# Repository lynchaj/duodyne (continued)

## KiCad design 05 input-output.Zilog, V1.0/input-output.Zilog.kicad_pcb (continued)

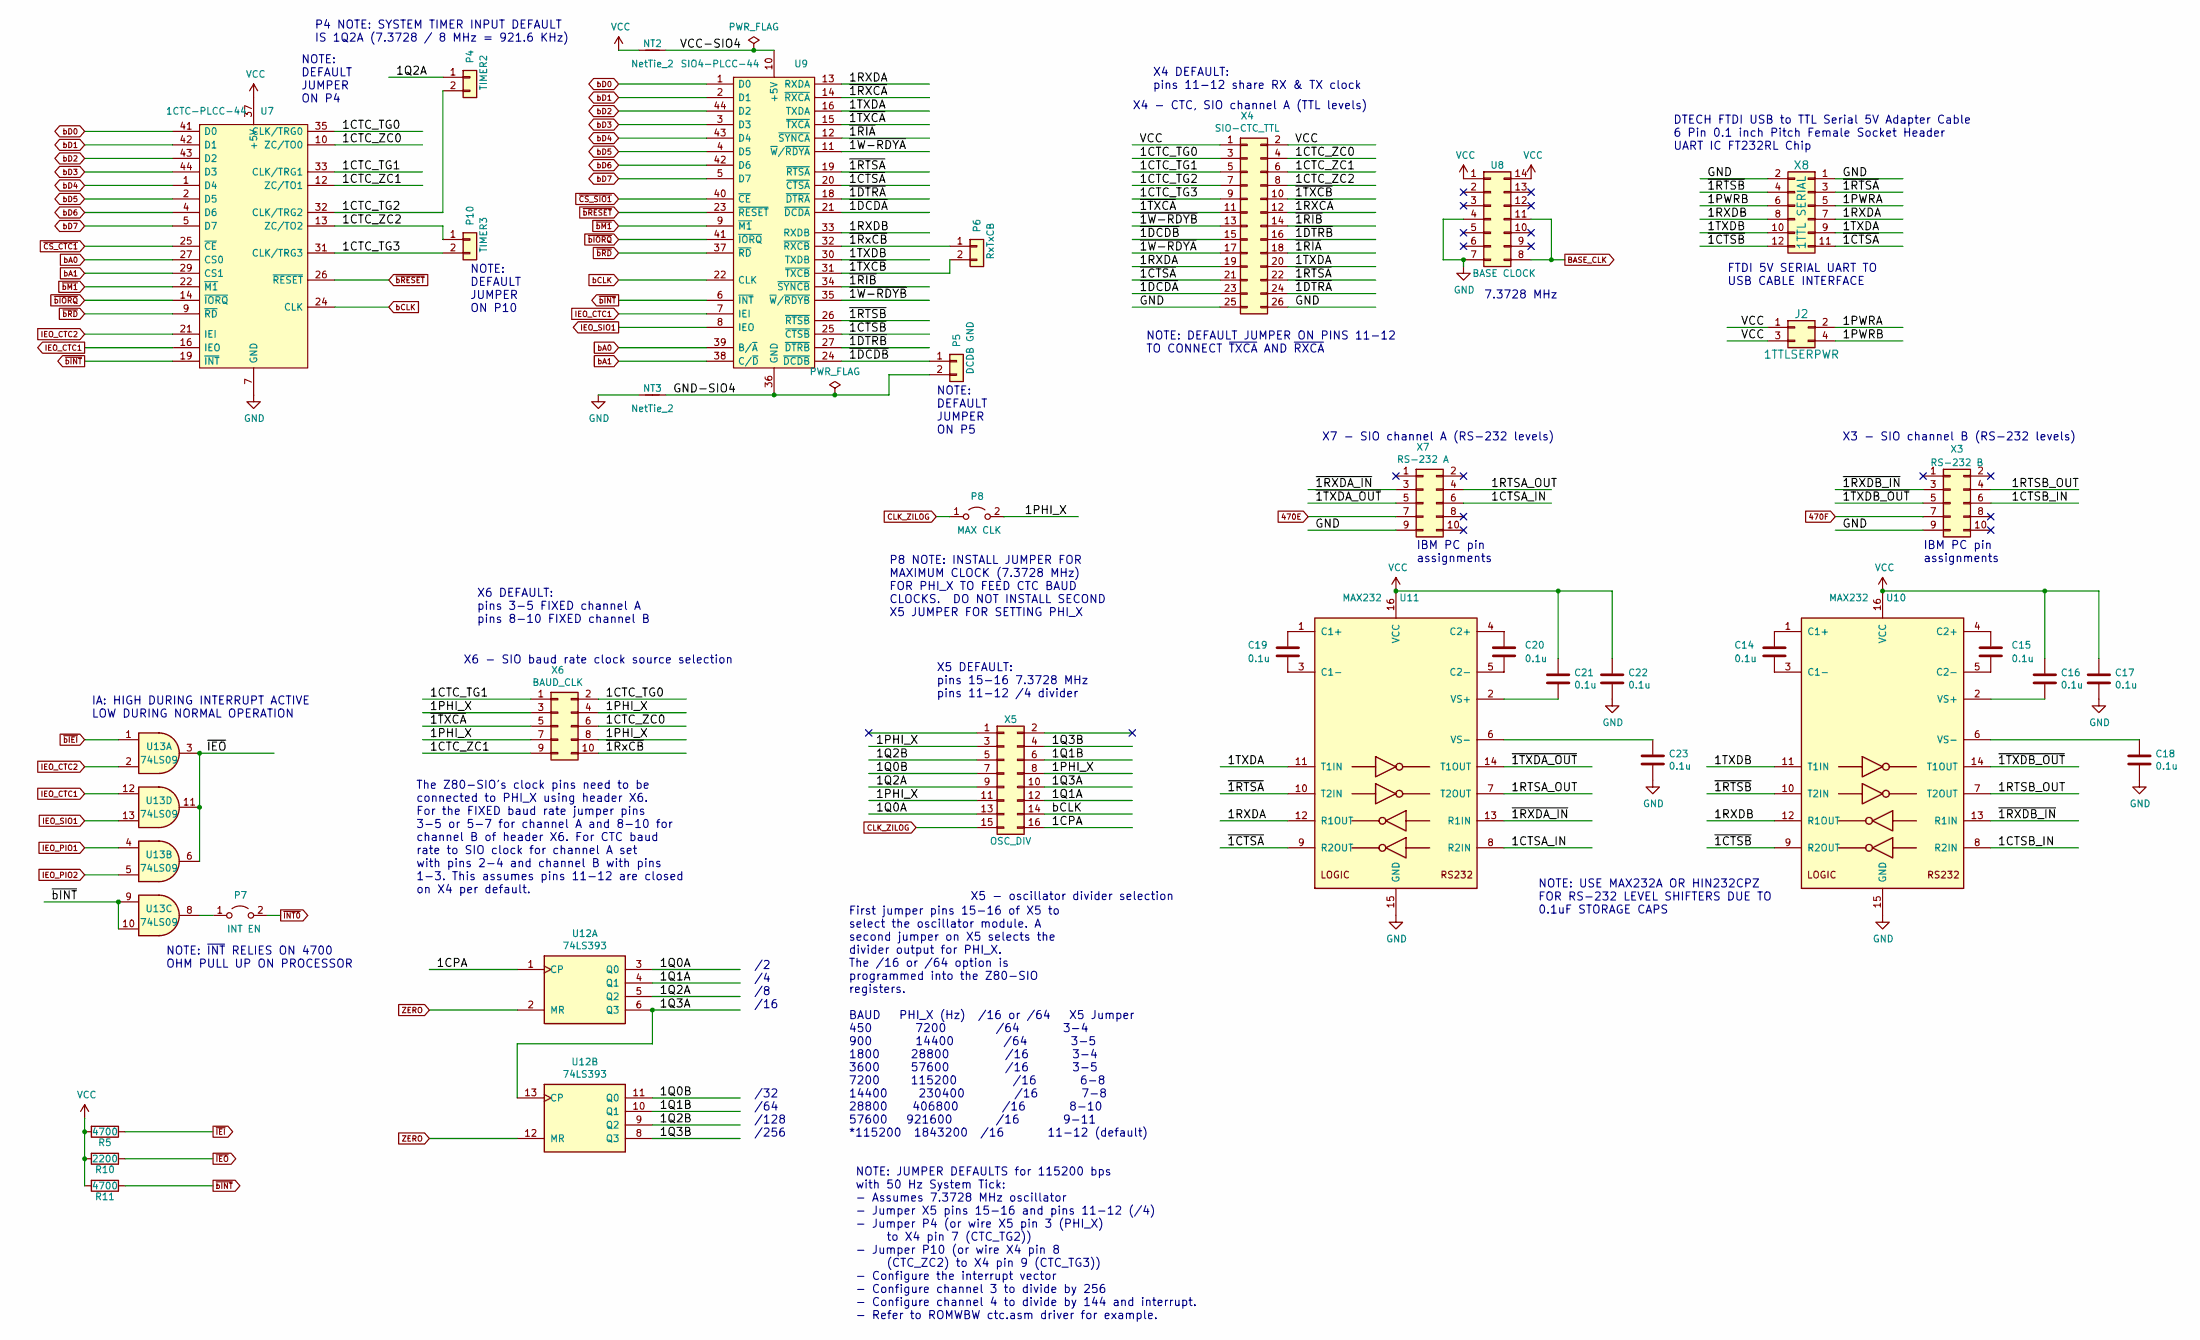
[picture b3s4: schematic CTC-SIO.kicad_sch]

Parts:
C14, C15, C16, C17, C18, C19, C20, C21, C22, C23: 0.1u; C_Disc_D5.0mm_W2.5mm_P5.00mm
J2: 1TTLSERPWR; PinHeader_2x02_P2.54mm_Vertical
NT2, NT3: NetTie_2; NetTie-2_THT_Pad0.3mm
P4: TIMER2; PinHeader_1x02_P2.54mm_Vertical
P5: DCDB GND; PinHeader_1x02_P2.54mm_Vertical
P6: RxTxCB; PinHeader_1x02_P2.54mm_Vertical
P7: INT EN; PinHeader_1x02_P2.54mm_Vertical
P8: MAX CLK; PinHeader_1x02_P2.54mm_Vertical
P10: TIMER3; PinHeader_1x02_P2.54mm_Vertical
R5, R11: 4700; R_Axial_DIN0207_L6.3mm_D2.5mm_P7.62mm_Horizontal
R10: 2200; R_Axial_DIN0207_L6.3mm_D2.5mm_P7.62mm_Horizontal
U7: 1CTC-PLCC-44; PLCC-44_THT-Socket; Manufacturer_Part_Number Z84C3010PEG; Mouser Part Number 692-Z84C3010PEG
U8: BASE CLOCK; DIP-14_W7.62mm
U9: SIO4-PLCC-44; PLCC-44_THT-Socket; Manufacturer_Part_Number Z84C4206PEG; Mouser Part Number 692-Z84C4206PEG
U10, U11: MAX232; DIP-16_W7.62mm
U12: 74LS393; DIP-14_W7.62mm
U13: 74LS09; DIP-14_W7.62mm
X3: RS-232 B; IDC-Header_2x05_P2.54mm_Horizontal
X4: SIO-CTC_TTL; PinHeader_2x13_P2.54mm_Vertical
X5: OSC_DIV; PinHeader_2x08_P2.54mm_Vertical
X6: BAUD_CLK; PinHeader_2x05_P2.54mm_Vertical
X7: RS-232 A; IDC-Header_2x05_P2.54mm_Horizontal
X8: 1TTL SERIAL; IDC-Header_2x06_P2.54mm_Horizontal

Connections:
470E: X7.7; also elsewhere on the board
470F: X3.7; also elsewhere on the board
/CTC-SIO/1CPA: U12.1 (CP), X5.16
/CTC-SIO/1CTC_TG0: U7.35 (CLK/TRG0), X4.3, X6.2
/CTC-SIO/1CTC_TG1: U7.33 (CLK/TRG1), X4.5, X6.1
/CTC-SIO/1CTC_TG2: P4.2, U7.32 (CLK/TRG2), X4.7
/CTC-SIO/1CTC_TG3: P10.2, U7.31 (CLK/TRG3), X4.9
/CTC-SIO/1CTC_ZC0: U7.10 (ZC/TO0), X4.4, X6.6
/CTC-SIO/1CTC_ZC1: U7.12 (ZC/TO1), X4.6, X6.9
/CTC-SIO/1CTC_ZC2: P10.1, U7.13 (ZC/TO2), X4.8
/CTC-SIO/1CTSA_IN: U11.8 (R2IN), X7.6
/CTC-SIO/1CTSB_IN: U10.8 (R2IN), X3.6
/CTC-SIO/1PHI_X: P8.2 (B), X5.3, X5.8, X5.11, X6.3, X6.4, X6.7, X6.8
/CTC-SIO/1PWRA: J2.2, X8.5
/CTC-SIO/1PWRB: J2.4, X8.6
/CTC-SIO/1Q0A: U12.3 (Q0), X5.13
/CTC-SIO/1Q0B: U12.11 (Q0), X5.7
/CTC-SIO/1Q1A: U12.4 (Q1), X5.12
/CTC-SIO/1Q1B: U12.10 (Q1), X5.6
/CTC-SIO/1Q2A: P4.1, U12.5 (Q2), X5.9
/CTC-SIO/1Q2B: U12.9 (Q2), X5.5
/CTC-SIO/1Q3A: U12.6 (Q3), U12.13 (CP), X5.10
/CTC-SIO/1Q3B: U12.8 (Q3), X5.4
/CTC-SIO/1RTSA_OUT: U11.7 (T2OUT), X7.4
/CTC-SIO/1RTSB_OUT: U10.7 (T2OUT), X3.4
/CTC-SIO/1RXDA: U9.13 (RXDA), U11.12 (R1OUT), X4.19, X8.7
/CTC-SIO/1RXDB: U9.33 (RXDB), U10.12 (R1OUT), X8.8
/CTC-SIO/1TXDA: U9.16 (TXDA), U11.11 (T1IN), X4.20, X8.9
/CTC-SIO/1TXDB: U9.30 (TXDB), U10.11 (T1IN), X8.10
/CTC-SIO/GND-SIO4: NT3.2, P5.2, U9.36 (GND)
/CTC-SIO/VCC-SIO4: NT2.2, U9.10 (+5V)
/CTC-SIO/~1CTSA: U9.20 (~CTSA), U11.9 (R2OUT), X4.21, X8.11
/CTC-SIO/~1CTSB: U9.25 (~CTSB), U10.9 (R2OUT), X8.12
/CTC-SIO/~1DCDA: U9.21 (~DCDA), X4.23
/CTC-SIO/~1DCDB: P5.1, U9.24 (~DCDB), X4.15
/CTC-SIO/~1DTRA: U9.18 (~DTRA), X4.24
/CTC-SIO/~1DTRB: U9.27 (~DTRB), X4.16
/CTC-SIO/~1RIA: U9.12 (~SYNCA), X4.18
/CTC-SIO/~1RIB: U9.34 (~SYNCB), X4.14
/CTC-SIO/~1RTSA: U9.19 (~RTSA), U11.10 (T2IN), X4.22, X8.3
/CTC-SIO/~1RTSB: U9.26 (~RTSB), U10.10 (T2IN), X8.4
/CTC-SIO/~1RXCA: U9.14 (~RXCA), X4.12
/CTC-SIO/~1RXDA_IN: U11.13 (R1IN), X7.3
/CTC-SIO/~1RXDB_IN: U10.13 (R1IN), X3.3
/CTC-SIO/~1RxCB: P6.1, U9.32 (~RXCB), X6.10
/CTC-SIO/~1TXCA: U9.15 (~TXCA), X4.11, X6.5
/CTC-SIO/~1TXCB: P6.2, U9.31 (~TXCB), X4.10
/CTC-SIO/~1TXDA_OUT: U11.14 (T1OUT), X7.5
/CTC-SIO/~1TXDB_OUT: U10.14 (T1OUT), X3.5
/CTC-SIO/~1W-RDYA: U9.11 (~W/~RDYA), X4.17
/CTC-SIO/~1W-RDYB: U9.35 (~W/~RDYB), X4.13
BASE_CLK: U8.8, U8.11; also elsewhere on the board
CLK_ZILOG: P8.1 (A), X5.15; also elsewhere on the board
GND: C17.2, C18.2, C22.2, C23.2, NT3.1, U7.7 (GND), U8.4, U8.7, U10.15 (GND), U11.15 (GND), X3.9, X4.25, X4.26, X7.9, X8.1, X8.2; also elsewhere on the board
IEO_CTC1: U7.16 (IEO), U9.7 (IEI), U13.12; also elsewhere on the board
IEO_CTC2: U7.21 (IEI), U13.2; also elsewhere on the board
IEO_PIO1: U13.4; also elsewhere on the board
IEO_PIO2: U13.5; also elsewhere on the board
IEO_SIO1: U9.8 (IEO), U13.13; also elsewhere on the board
unnamed: C14.1, U10.1 (C1+)
unnamed: C14.2, U10.3 (C1-)
unnamed: C15.1, U10.4 (C2+)
unnamed: C15.2, U10.5 (C2-)
unnamed: C16.2, U10.2 (VS+)
unnamed: C18.1, U10.6 (VS-)
unnamed: C19.1, U11.1 (C1+)
unnamed: C19.2, U11.3 (C1-)
unnamed: C20.1, U11.4 (C2+)
unnamed: C20.2, U11.5 (C2-)
unnamed: C21.2, U11.2 (VS+)
unnamed: C23.1, U11.6 (VS-)
unnamed: P7.1 (A), U13.8
VCC: C16.1, C17.1, C21.1, C22.1, J2.1, J2.3, NT2.1, R5.2, R10.2, R11.2, U7.37 (+5V), U8.1, U8.14, U10.16 (VCC), U11.16 (VCC), X4.1, X4.2; also elsewhere on the board
ZERO: U12.2 (MR), U12.12 (MR); also elsewhere on the board
bA0: U7.27 (CS0), U9.39 (B/~A); also elsewhere on the board
bA1: U7.29 (CS1), U9.38 (C/~D); also elsewhere on the board
bCLK: U7.24 (CLK), U9.22 (CLK), X5.14; also elsewhere on the board
bD0: U7.41 (D0), U9.1 (D0); also elsewhere on the board
bD1: U7.42 (D1), U9.2 (D1); also elsewhere on the board
bD2: U7.43 (D2), U9.44 (D2); also elsewhere on the board
bD3: U7.44 (D3), U9.3 (D3); also elsewhere on the board
bD4: U7.1 (D4), U9.43 (D4); also elsewhere on the board
bD5: U7.2 (D5), U9.4 (D5); also elsewhere on the board
bD6: U7.4 (D6), U9.42 (D6); also elsewhere on the board
bD7: U7.5 (D7), U9.5 (D7); also elsewhere on the board
~CS_CTC1: U7.25 (~CE); also elsewhere on the board
~CS_SIO1: U9.40 (~CE); also elsewhere on the board
~IEI: R5.1; also elsewhere on the board
~IEO: R10.1, U13.3, U13.6, U13.11; also elsewhere on the board
~INT0: P7.2 (B); also elsewhere on the board
~bIEI: U13.1; also elsewhere on the board
~bINT: R11.1, U7.19 (~INT), U9.6 (~INT), U13.9, U13.10; also elsewhere on the board
~bIORQ: U7.14 (~IORQ), U9.41 (~IORQ); also elsewhere on the board
~bM1: U7.22 (~M1), U9.9 (~M1); also elsewhere on the board
~bRD: U7.9 (~RD), U9.37 (~RD); also elsewhere on the board
~bRESET: U7.26 (~RESET), U9.23 (~RESET); also elsewhere on the board

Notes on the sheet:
NOTE: JUMPER DEFAULTS for 115200 bps with 50 Hz System Tick: - Assumes 7.3728 MHz oscillator - Jumper X5 pins 15-16 and pins 11-12 (/4) - Jumper P4 (or wire X5 pin 3 (PHI_X) to X4 pin 7 (CTC_TG2)) - Jumper P10 (or wire X4 pin 8 (CTC_ZC2) to X4 pin 9 (CTC_TG3)) - Configure the interrupt vector - Con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
X3 - SIO channel B (RS-232 levels)
The Z80-SIO's clock pins need to be connected to PHI_X using header X6. For the FIXED baud rate jumper pins 3-5 or 5-7 for channel A and 8-10 for channel B of header X6. For CTC baud rate to SIO clock for channel A set with pins 2-4 and channel B with pins 1-3. This assumes pins 11-12 are closed on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
X7 - SIO channel A (RS-232 levels)
DTECH FTDI USB to TTL Serial 5V Adapter Cable 6 Pin 0.1 inch Pitch Female Socket Header UART IC FT232RL Chip
NOTE: DEFAULT JUMPER ON P4
/32 /64 /128 /256
7.3728 MHz
NOTE: ~{INT} RELIES ON 4700 OHM PULL UP ON PROCESSOR
X5 - oscillator divider selection
FTDI 5V SERIAL UART TO USB CABLE INTERFACE
IBM PC pin assignments
P4 NOTE: SYSTEM TIMER INPUT DEFAULT IS 1Q2A (7.3728 / 8 MHz = 921.6 KHz)
IA: HIGH DURING INTERRUPT ACTIVE LOW DURING NORMAL OPERATION
NOTE: DEFAULT JUMPER ON P10
X5 DEFAULT: pins 15-16 7.3728 MHz pins 11-12 /4 divider
/2 /4 /8 /16
First jumper pins 15-16 of X5 to select the oscillator module. A second jumper on X5 selects the divider output for PHI_X. The /16 or /64 option is programmed into the Z80-SIO registers. BAUD PHI_X (Hz) /16 or /64 X5 Jumper 450 7200 /64 3-4 900 14400 /64 3-5 1800 28800 /16 3-4 3600 57600 /16 3-5 72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
NOTE: DEFAULT JUMPER ON PINS 11-12 TO CONNECT ~{TXCA} AND ~{RXCA}
X4 - CTC, SIO channel A (TTL levels)
NOTE: USE MAX232A OR HIN232CPZ FOR RS-232 LEVEL SHIFTERS DUE TO 0.1uF STORAGE CAPS
P8 NOTE: INSTALL JUMPER FOR MAXIMUM CLOCK (7.3728 MHz) FOR PHI_X TO FEED CTC BAUD CLOCKS. DO NOT INSTALL SECOND X5 JUMPER FOR SETTING PHI_X
X6 DEFAULT: pins 3-5 FIXED channel A pins 8-10 FIXED channel B
X6 - SIO baud rate clock source selection
X4 DEFAULT: pins 11-12 share RX & TX clock
NOTE: DEFAULT JUMPER ON P5

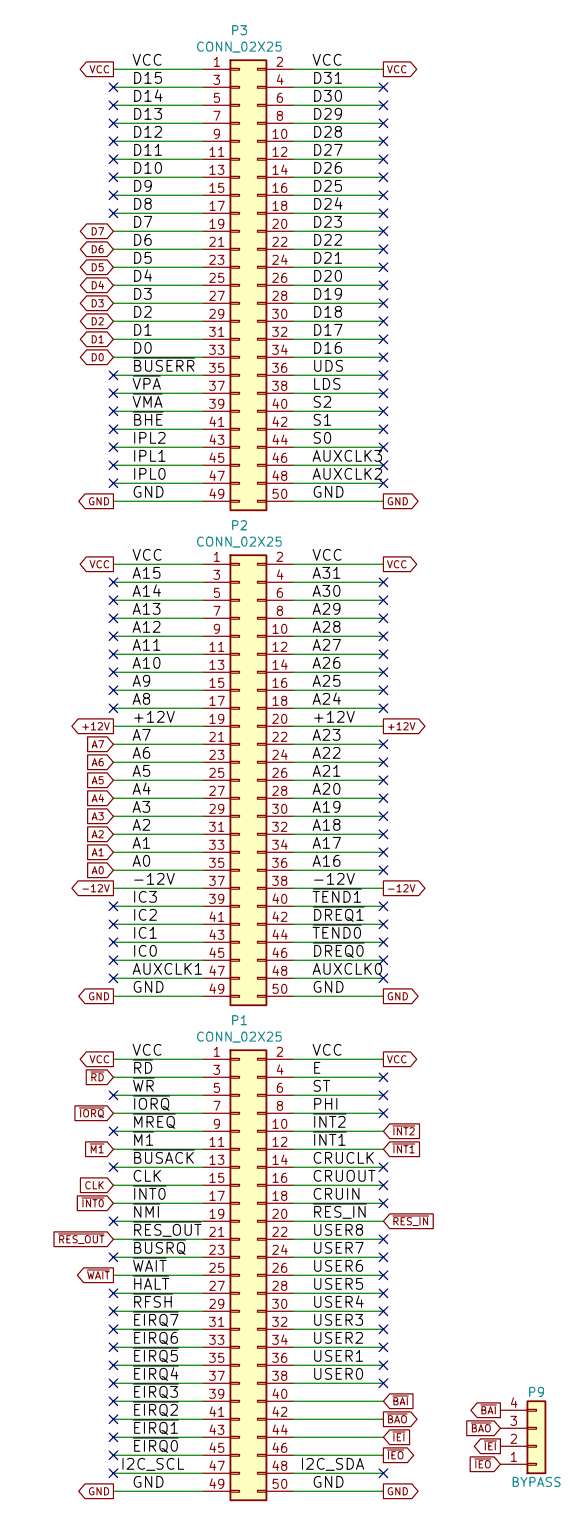
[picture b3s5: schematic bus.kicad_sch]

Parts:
P1, P2, P3: CONN_02X25; IDC-Header_2x25_P2.54mm_Horizontal
P9: BYPASS; PinHeader_1x04_P2.54mm_Vertical

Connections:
+12V: P2.19, P2.20
-12V: P2.37, P2.38
/bus/A8: P2.17
/bus/A9: P2.15
/bus/A10: P2.13
/bus/A11: P2.11
/bus/A12: P2.9
/bus/A13: P2.7
/bus/A14: P2.5
/bus/A15: P2.3
/bus/A16: P2.36
/bus/A17: P2.34
/bus/A18: P2.32
/bus/A19: P2.30
/bus/A20: P2.28
/bus/A21: P2.26
/bus/A22: P2.24
/bus/A23: P2.22
/bus/A24: P2.18
/bus/A25: P2.16
/bus/A26: P2.14
/bus/A27: P2.12
/bus/A28: P2.10
/bus/A29: P2.8
/bus/A30: P2.6
/bus/A31: P2.4
/bus/AUXCLK0: P2.48
/bus/AUXCLK1: P2.47
/bus/AUXCLK2: P3.48
/bus/AUXCLK3: P3.46
/bus/CRUCLK: P1.14
/bus/CRUIN: P1.18
/bus/CRUOUT: P1.16
/bus/D8: P3.17
/bus/D9: P3.15
/bus/D10: P3.13
/bus/D11: P3.11
/bus/D12: P3.9
/bus/D13: P3.7
/bus/D14: P3.5
/bus/D15: P3.3
/bus/D16: P3.34
/bus/D17: P3.32
/bus/D18: P3.30
/bus/D19: P3.28
/bus/D20: P3.26
/bus/D21: P3.24
/bus/D22: P3.22
/bus/D23: P3.20
/bus/D24: P3.18
/bus/D25: P3.16
/bus/D26: P3.14
/bus/D27: P3.12
/bus/D28: P3.10
/bus/D29: P3.8
/bus/D30: P3.6
/bus/D31: P3.4
/bus/E: P1.4
/bus/I2C_SCL: P1.47
/bus/I2C_SDA: P1.48
/bus/IC0: P2.45
/bus/IC1: P2.43
/bus/IC2: P2.41
/bus/IC3: P2.39
/bus/IPL0: P3.47
/bus/IPL1: P3.45
/bus/IPL2: P3.43
/bus/LDS: P3.38
/bus/PHI: P1.8
/bus/S0: P3.44
/bus/S1: P3.42
/bus/S2: P3.40
/bus/ST: P1.6
/bus/UDS: P3.36
/bus/USER0: P1.38
/bus/USER1: P1.36
/bus/USER2: P1.34
/bus/USER3: P1.32
/bus/USER4: P1.30
/bus/USER5: P1.28
/bus/USER6: P1.26
/bus/USER7: P1.24
/bus/USER8: P1.22
/bus/~BHE: P3.41
/bus/~BUSACK: P1.13
/bus/~BUSERR: P3.35
/bus/~BUSRQ: P1.23
/bus/~DREQ0: P2.46
/bus/~DREQ1: P2.42
/bus/~EIRQ0: P1.45
/bus/~EIRQ1: P1.43
/bus/~EIRQ2: P1.41
/bus/~EIRQ3: P1.39
/bus/~EIRQ4: P1.37
/bus/~EIRQ5: P1.35
/bus/~EIRQ6: P1.33
/bus/~EIRQ7: P1.31
/bus/~HALT: P1.27
/bus/~MREQ: P1.9
/bus/~NMI: P1.19
/bus/~RFSH: P1.29
/bus/~TEND0: P2.44
/bus/~TEND1: P2.40
/bus/~VMA: P3.39
/bus/~VPA: P3.37
/bus/~WR: P1.5
A0: P2.35; also elsewhere on the board
A1: P2.33; also elsewhere on the board
A2: P2.31; also elsewhere on the board
A3: P2.29; also elsewhere on the board
A4: P2.27; also elsewhere on the board
A5: P2.25; also elsewhere on the board
A6: P2.23; also elsewhere on the board
A7: P2.21; also elsewhere on the board
CLK: P1.15; also elsewhere on the board
D0: P3.33; also elsewhere on the board
D1: P3.31; also elsewhere on the board
D2: P3.29; also elsewhere on the board
D3: P3.27; also elsewhere on the board
D4: P3.25; also elsewhere on the board
D5: P3.23; also elsewhere on the board
D6: P3.21; also elsewhere on the board
D7: P3.19; also elsewhere on the board
GND: P1.49, P1.50, P2.49, P2.50, P3.49, P3.50; also elsewhere on the board
VCC: P1.1, P1.2, P2.1, P2.2, P3.1, P3.2; also elsewhere on the board
~BAI: P1.40, P9.4
~BAO: P1.42, P9.3
~IEI: P1.44, P9.2; also elsewhere on the board
~IEO: P1.46, P9.1; also elsewhere on the board
~INT0: P1.17; also elsewhere on the board
~INT1: P1.12; also elsewhere on the board
~INT2: P1.10; also elsewhere on the board
~IORQ: P1.7; also elsewhere on the board
~M1: P1.11; also elsewhere on the board
~RD: P1.3; also elsewhere on the board
~RES_IN: P1.20; also elsewhere on the board
~RES_OUT: P1.21; also elsewhere on the board
~WAIT: P1.25; also elsewhere on the board

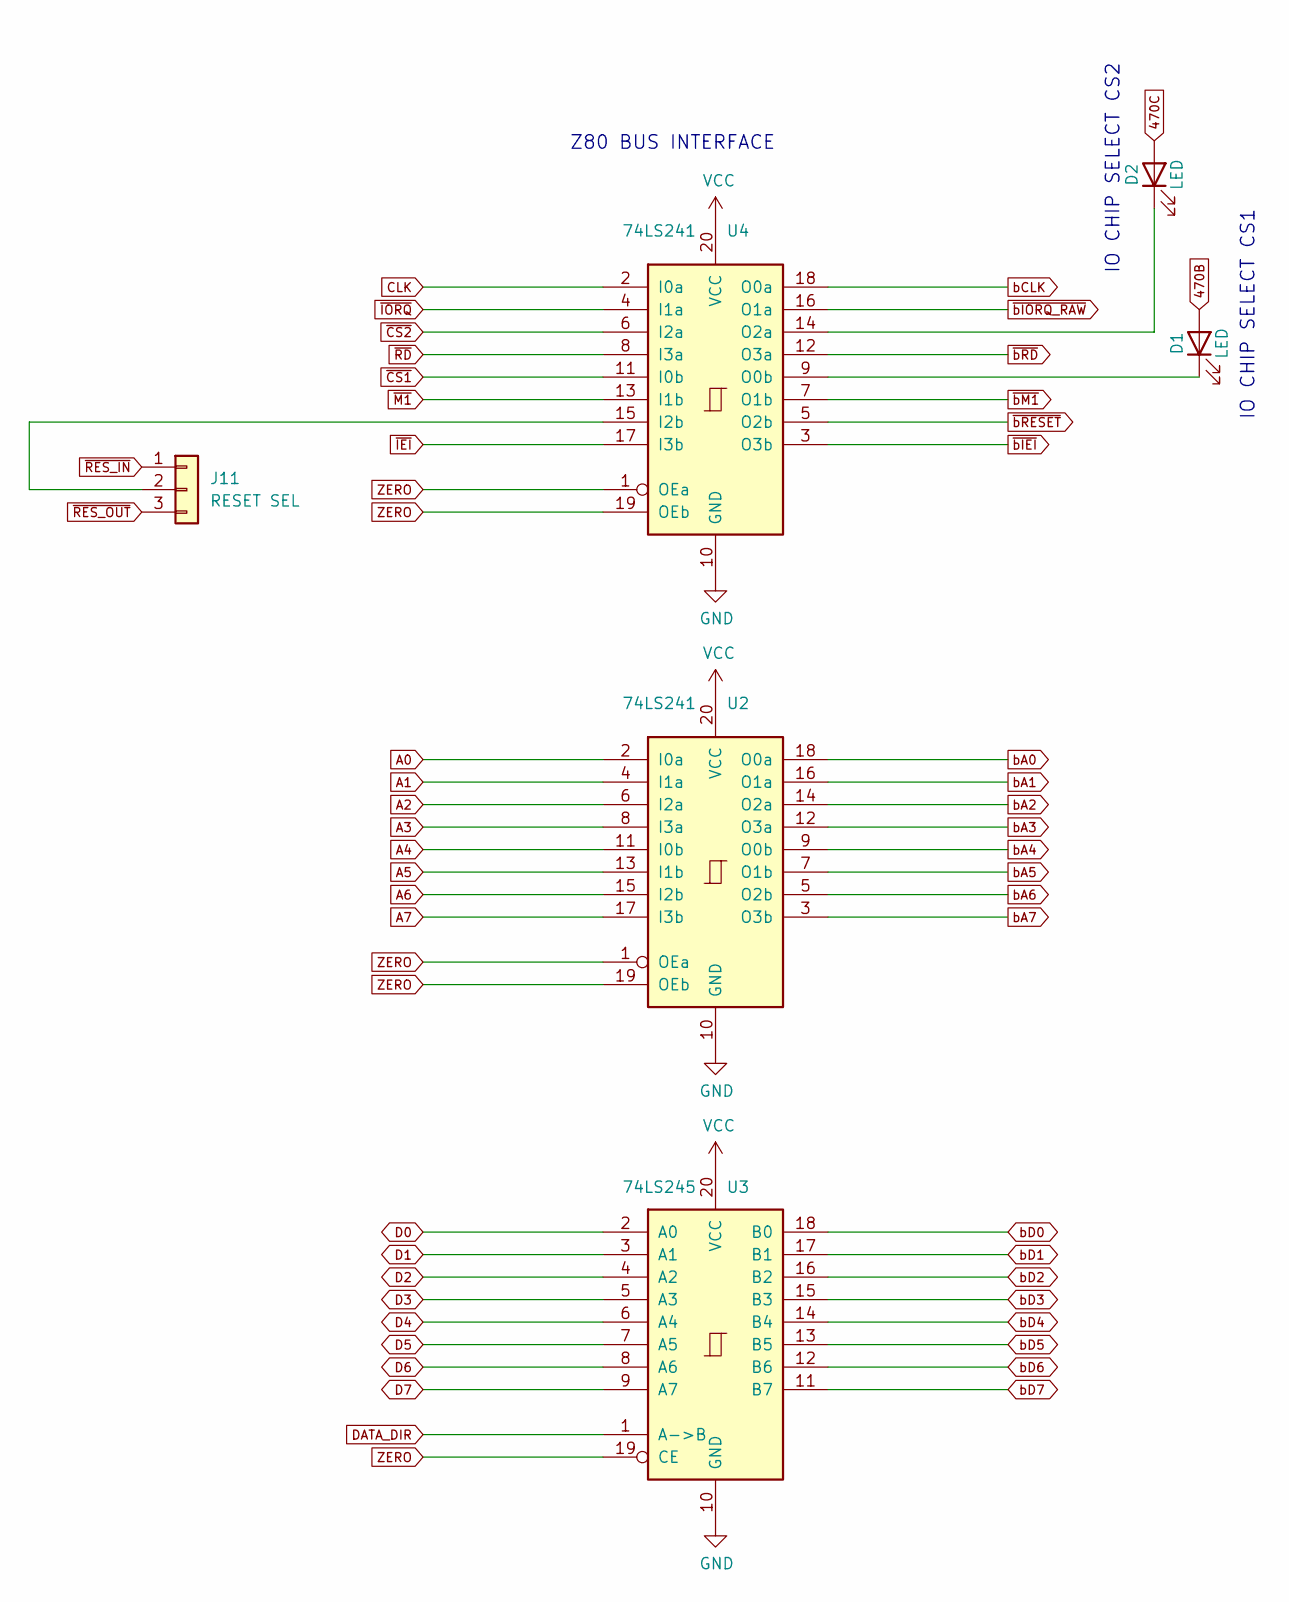
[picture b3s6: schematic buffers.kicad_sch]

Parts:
D1, D2: LED; LED_D3.0mm_Horizontal_O3.81mm_Z2.0mm
J11: RESET SEL; PinHeader_1x03_P2.54mm_Vertical
U2, U4: 74LS241; DIP-20_W7.62mm
U3: 74LS245; DIP-20_W7.62mm

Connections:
470B: D1.2 (A); also elsewhere on the board
470C: D2.2 (A); also elsewhere on the board
A0: U2.2 (I0a); also elsewhere on the board
A1: U2.4 (I1a); also elsewhere on the board
A2: U2.6 (I2a); also elsewhere on the board
A3: U2.8 (I3a); also elsewhere on the board
A4: U2.11 (I0b); also elsewhere on the board
A5: U2.13 (I1b); also elsewhere on the board
A6: U2.15 (I2b); also elsewhere on the board
A7: U2.17 (I3b); also elsewhere on the board
CLK: U4.2 (I0a); also elsewhere on the board
D0: U3.2 (A0); also elsewhere on the board
D1: U3.3 (A1); also elsewhere on the board
D2: U3.4 (A2); also elsewhere on the board
D3: U3.5 (A3); also elsewhere on the board
D4: U3.6 (A4); also elsewhere on the board
D5: U3.7 (A5); also elsewhere on the board
D6: U3.8 (A6); also elsewhere on the board
D7: U3.9 (A7); also elsewhere on the board
DATA_DIR: U3.1 (A->B); also elsewhere on the board
GND: U2.10 (GND), U3.10 (GND), U4.10 (GND); also elsewhere on the board
unnamed: D1.1 (K), U4.9 (O0b)
unnamed: D2.1 (K), U4.14 (O2a)
unnamed: J11.2, U4.15 (I2b)
VCC: U2.20 (VCC), U3.20 (VCC), U4.20 (VCC); also elsewhere on the board
ZERO: U2.1 (OEa), U2.19 (OEb), U3.19 (CE), U4.1 (OEa), U4.19 (OEb); also elsewhere on the board
bA0: U2.18 (O0a); also elsewhere on the board
bA1: U2.16 (O1a); also elsewhere on the board
bA2: U2.14 (O2a); also elsewhere on the board
bA3: U2.12 (O3a); also elsewhere on the board
bA4: U2.9 (O0b); also elsewhere on the board
bA5: U2.7 (O1b); also elsewhere on the board
bA6: U2.5 (O2b); also elsewhere on the board
bA7: U2.3 (O3b); also elsewhere on the board
bCLK: U4.18 (O0a); also elsewhere on the board
bD0: U3.18 (B0); also elsewhere on the board
bD1: U3.17 (B1); also elsewhere on the board
bD2: U3.16 (B2); also elsewhere on the board
bD3: U3.15 (B3); also elsewhere on the board
bD4: U3.14 (B4); also elsewhere on the board
bD5: U3.13 (B5); also elsewhere on the board
bD6: U3.12 (B6); also elsewhere on the board
bD7: U3.11 (B7); also elsewhere on the board
~CS1: U4.11 (I0b); also elsewhere on the board
~CS2: U4.6 (I2a); also elsewhere on the board
~IEI: U4.17 (I3b); also elsewhere on the board
~IORQ: U4.4 (I1a); also elsewhere on the board
~M1: U4.13 (I1b); also elsewhere on the board
~RD: U4.8 (I3a); also elsewhere on the board
~RES_IN: J11.1; also elsewhere on the board
~RES_OUT: J11.3; also elsewhere on the board
~bIEI: U4.3 (O3b); also elsewhere on the board
~bIORQ_RAW: U4.16 (O1a); also elsewhere on the board
~bM1: U4.7 (O1b); also elsewhere on the board
~bRD: U4.12 (O3a); also elsewhere on the board
~bRESET: U4.5 (O2b); also elsewhere on the board

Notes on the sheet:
IO CHIP SELECT CS1
Z80 BUS INTERFACE
IO CHIP SELECT CS2

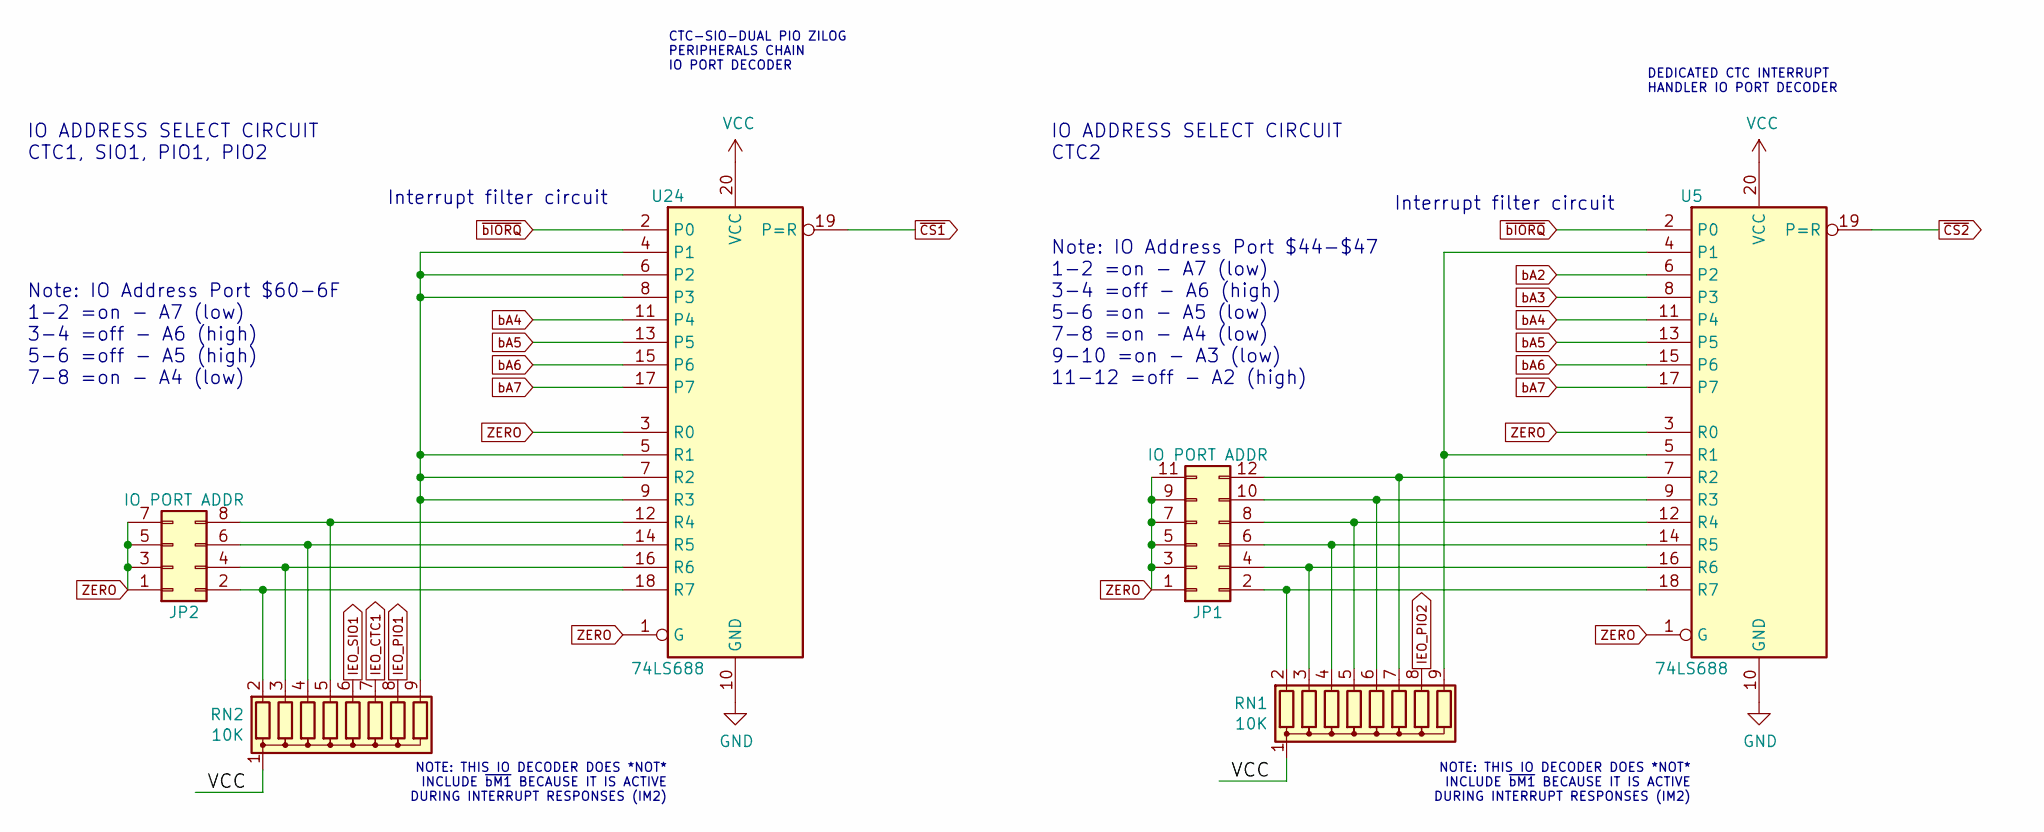
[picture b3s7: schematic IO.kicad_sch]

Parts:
JP1: IO PORT ADDR; PinHeader_2x06_P2.54mm_Vertical
JP2: IO PORT ADDR; PinHeader_2x04_P2.54mm_Vertical
RN1, RN2: 10K; R_Array_SIP9
U5, U24: 74LS688; DIP-20_W7.62mm

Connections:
GND: U5.10 (GND), U24.10 (GND); also elsewhere on the board
IEO_CTC1: RN2.7 (R6); also elsewhere on the board
IEO_PIO1: RN2.8 (R7); also elsewhere on the board
IEO_PIO2: RN1.8 (R7); also elsewhere on the board
IEO_SIO1: RN2.6 (R5); also elsewhere on the board
unnamed: JP1.2, RN1.2 (R1), U5.18 (R7)
unnamed: JP1.4, RN1.3 (R2), U5.16 (R6)
unnamed: JP1.6, RN1.4 (R3), U5.14 (R5)
unnamed: JP1.8, RN1.5 (R4), U5.12 (R4)
unnamed: JP1.10, RN1.6 (R5), U5.9 (R3)
unnamed: JP1.12, RN1.7 (R6), U5.7 (R2)
unnamed: JP2.2, RN2.2 (R1), U24.18 (R7)
unnamed: JP2.4, RN2.3 (R2), U24.16 (R6)
unnamed: JP2.6, RN2.4 (R3), U24.14 (R5)
unnamed: JP2.8, RN2.5 (R4), U24.12 (R4)
unnamed: RN1.9 (R8), U5.4 (P1), U5.5 (R1)
unnamed: RN2.9 (R8), U24.4 (P1), U24.5 (R1), U24.6 (P2), U24.7 (R2), U24.8 (P3), U24.9 (R3)
VCC: RN1.1 (common), RN2.1 (common), U5.20 (VCC), U24.20 (VCC); also elsewhere on the board
ZERO: JP1.1, JP1.3, JP1.5, JP1.7, JP1.9, JP1.11, JP2.1, JP2.3, JP2.5, JP2.7, U5.1 (G), U5.3 (R0), U24.1 (G), U24.3 (R0); also elsewhere on the board
bA2: U5.6 (P2); also elsewhere on the board
bA3: U5.8 (P3); also elsewhere on the board
bA4: U5.11 (P4), U24.11 (P4); also elsewhere on the board
bA5: U5.13 (P5), U24.13 (P5); also elsewhere on the board
bA6: U5.15 (P6), U24.15 (P6); also elsewhere on the board
bA7: U5.17 (P7), U24.17 (P7); also elsewhere on the board
~CS1: U24.19 (P=R); also elsewhere on the board
~CS2: U5.19 (P=R); also elsewhere on the board
~bIORQ: U5.2 (P0), U24.2 (P0); also elsewhere on the board

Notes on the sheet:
IO ADDRESS SELECT CIRCUIT CTC1, SIO1, PIO1, PIO2
Note: IO Address Port $44-$47 1-2 =on - A7 (low) 3-4 =off - A6 (high) 5-6 =on - A5 (low) 7-8 =on - A4 (low) 9-10 =on - A3 (low) 11-12 =off - A2 (high)
IO ADDRESS SELECT CIRCUIT CTC2
DEDICATED CTC INTERRUPT HANDLER IO PORT DECODER
Interrupt filter circuit
Note: IO Address Port $60-6F 1-2 =on - A7 (low) 3-4 =off - A6 (high) 5-6 =off - A5 (high) 7-8 =on - A4 (low)
NOTE: THIS IO DECODER DOES *NOT* INCLUDE ~{bM1} BECAUSE IT IS ACTIVE DURING INTERRUPT RESPONSES (IM2)
CTC-SIO-DUAL PIO ZILOG PERIPHERALS CHAIN IO PORT DECODER

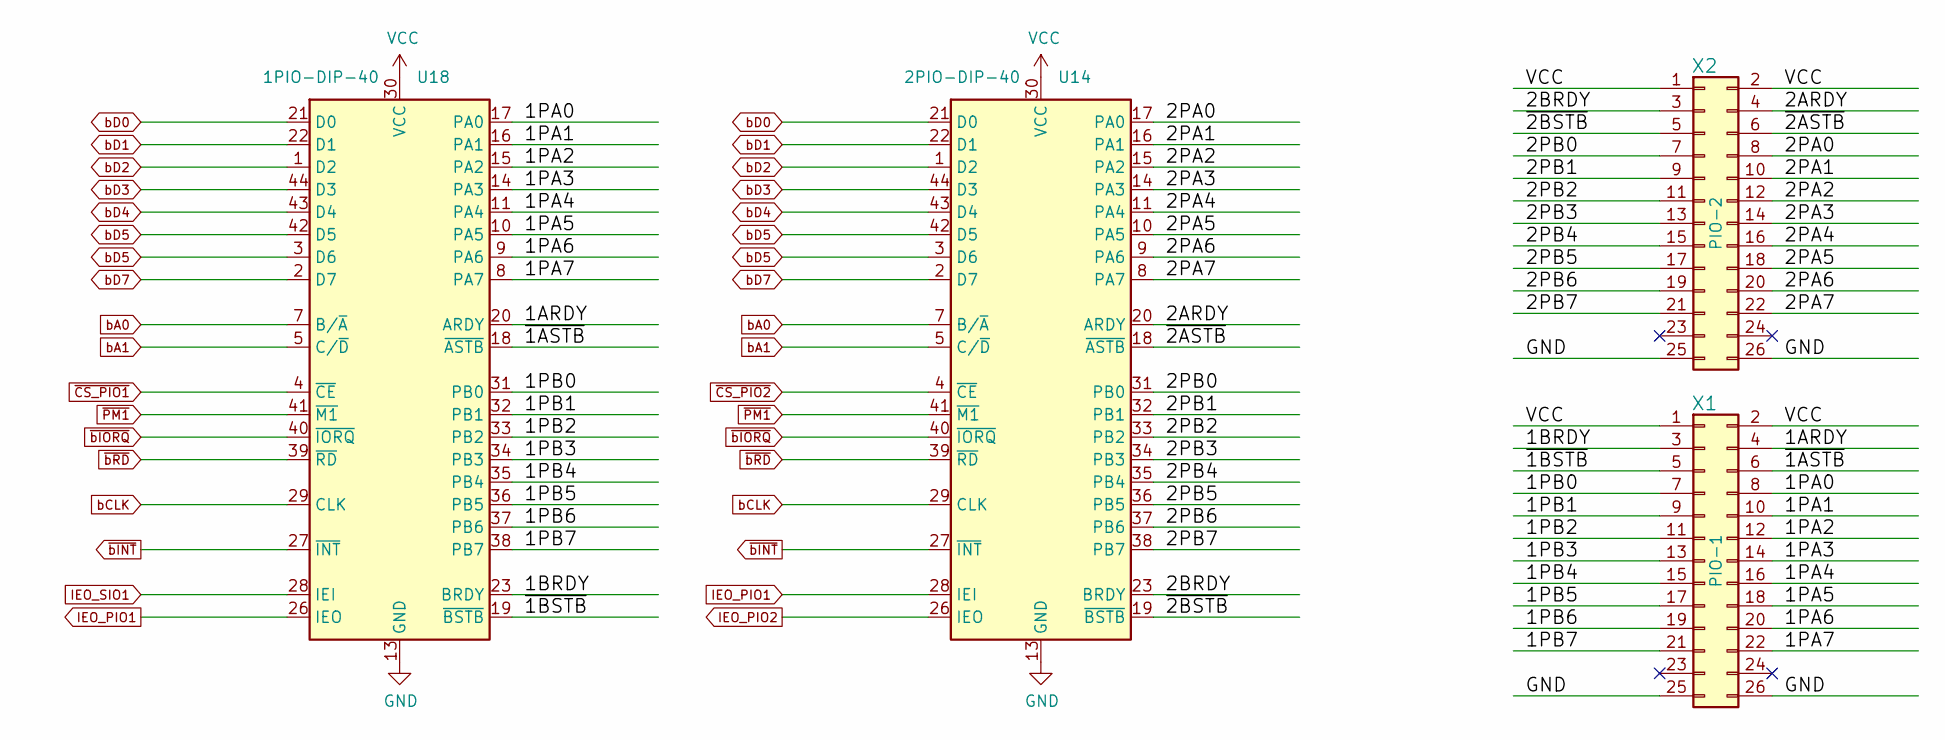
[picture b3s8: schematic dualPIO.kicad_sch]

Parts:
U14: 2PIO-DIP-40; PLCC-44_16.6x16.6mm_P1.27mm
U18: 1PIO-DIP-40; PLCC-44_16.6x16.6mm_P1.27mm
X1: PIO-1; IDC-Header_2x13_P2.54mm_Horizontal
X2: PIO-2; IDC-Header_2x13_P2.54mm_Horizontal

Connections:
/dualPIO/1ARDY: U18.20 (ARDY), X1.4
/dualPIO/1BRDY: U18.23 (BRDY), X1.3
/dualPIO/1PA0: U18.17 (PA0), X1.8
/dualPIO/1PA1: U18.16 (PA1), X1.10
/dualPIO/1PA2: U18.15 (PA2), X1.12
/dualPIO/1PA3: U18.14 (PA3), X1.14
/dualPIO/1PA4: U18.11 (PA4), X1.16
/dualPIO/1PA5: U18.10 (PA5), X1.18
/dualPIO/1PA6: U18.9 (PA6), X1.20
/dualPIO/1PA7: U18.8 (PA7), X1.22
/dualPIO/1PB0: U18.31 (PB0), X1.7
/dualPIO/1PB1: U18.32 (PB1), X1.9
/dualPIO/1PB2: U18.33 (PB2), X1.11
/dualPIO/1PB3: U18.34 (PB3), X1.13
/dualPIO/1PB4: U18.35 (PB4), X1.15
/dualPIO/1PB5: U18.36 (PB5), X1.17
/dualPIO/1PB6: U18.37 (PB6), X1.19
/dualPIO/1PB7: U18.38 (PB7), X1.21
/dualPIO/2ARDY: U14.20 (ARDY), X2.4
/dualPIO/2BRDY: U14.23 (BRDY), X2.3
/dualPIO/2PA0: U14.17 (PA0), X2.8
/dualPIO/2PA1: U14.16 (PA1), X2.10
/dualPIO/2PA2: U14.15 (PA2), X2.12
/dualPIO/2PA3: U14.14 (PA3), X2.14
/dualPIO/2PA4: U14.11 (PA4), X2.16
/dualPIO/2PA5: U14.10 (PA5), X2.18
/dualPIO/2PA6: U14.9 (PA6), X2.20
/dualPIO/2PA7: U14.8 (PA7), X2.22
/dualPIO/2PB0: U14.31 (PB0), X2.7
/dualPIO/2PB1: U14.32 (PB1), X2.9
/dualPIO/2PB2: U14.33 (PB2), X2.11
/dualPIO/2PB3: U14.34 (PB3), X2.13
/dualPIO/2PB4: U14.35 (PB4), X2.15
/dualPIO/2PB5: U14.36 (PB5), X2.17
/dualPIO/2PB6: U14.37 (PB6), X2.19
/dualPIO/2PB7: U14.38 (PB7), X2.21
/dualPIO/~1ASTB: U18.18 (~ASTB), X1.6
/dualPIO/~1BSTB: U18.19 (~BSTB), X1.5
/dualPIO/~2ASTB: U14.18 (~ASTB), X2.6
/dualPIO/~2BSTB: U14.19 (~BSTB), X2.5
GND: U14.13 (GND), U18.13 (GND), X1.25, X1.26, X2.25, X2.26; also elsewhere on the board
IEO_PIO1: U14.28 (IEI), U18.26 (IEO); also elsewhere on the board
IEO_PIO2: U14.26 (IEO); also elsewhere on the board
IEO_SIO1: U18.28 (IEI); also elsewhere on the board
VCC: U14.30 (VCC), U18.30 (VCC), X1.1, X1.2, X2.1, X2.2; also elsewhere on the board
bA0: U14.7 (B/~A), U18.7 (B/~A); also elsewhere on the board
bA1: U14.5 (C/~D), U18.5 (C/~D); also elsewhere on the board
bCLK: U14.29 (CLK), U18.29 (CLK); also elsewhere on the board
bD0: U14.21 (D0), U18.21 (D0); also elsewhere on the board
bD1: U14.22 (D1), U18.22 (D1); also elsewhere on the board
bD2: U14.1 (D2), U18.1 (D2); also elsewhere on the board
bD3: U14.44 (D3), U18.44 (D3); also elsewhere on the board
bD4: U14.43 (D4), U18.43 (D4); also elsewhere on the board
bD5: U14.3 (D6), U14.42 (D5), U18.3 (D6), U18.42 (D5); also elsewhere on the board
bD7: U14.2 (D7), U18.2 (D7); also elsewhere on the board
~CS_PIO1: U18.4 (~CE); also elsewhere on the board
~CS_PIO2: U14.4 (~CE); also elsewhere on the board
~PM1: U14.41 (~M1), U18.41 (~M1); also elsewhere on the board
~bINT: U14.27 (~INT), U18.27 (~INT); also elsewhere on the board
~bIORQ: U14.40 (~IORQ), U18.40 (~IORQ); also elsewhere on the board
~bRD: U14.39 (~RD), U18.39 (~RD); also elsewhere on the board

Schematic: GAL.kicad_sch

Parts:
D3: LED; LED_D3.0mm_Horizontal_O3.81mm_Z2.0mm
JP3: IA WS; PinHeader_2x04_P2.54mm_Vertical
JP4: WAIT EN; PinHeader_1x02_P2.54mm_Vertical
RN3: 10K; R_Array_SIP9
U1: GAL22V10; DIP-24_W7.62mm
U17: 74LS191; DIP-16_W7.62mm
U20: 74LS07
U21: GAL16V8; DIP-20_W7.62mm

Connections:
470D: D3.2 (A); also elsewhere on the board
/GAL/DEL_CNT: U17.7 (Q3), U21.3 (I3)
/GAL/bM1: U17.11 (Pl), U21.17 (I03)
/GAL/~bCLK: U17.14 (Cp), U21.16 (IO4)
/GAL/~bWAIT: U20.1, U21.18 (IO2)
BASE_CLK: U1.11 (I10); also elsewhere on the board
CLK_ZILOG: U1.17 (O6); also elsewhere on the board
DATA_DIR: U1.22 (O1); also elsewhere on the board
GND: U1.12 (GND), U17.8 (GND), U21.10 (GND); also elsewhere on the board
unnamed: JP3.2, RN3.2 (R1), U17.15 (P0)
unnamed: JP3.4, RN3.3 (R2), U17.1
unnamed: JP3.6, RN3.4 (R3), U17.10 (P2)
unnamed: JP3.8, RN3.5 (R4), U17.9 (P3)
unnamed: JP4.1 (A), U20.2
VCC: RN3.1 (common), U1.24 (VCC), U17.16 (VCC), U21.20 (VCC); also elsewhere on the board
ZERO: JP3.1, JP3.3, JP3.5, JP3.7, U17.4 (Ce), U17.5 (D/U); also elsewhere on the board
bA2: U1.9 (I8); also elsewhere on the board
bA3: U1.10 (I9); also elsewhere on the board
bCLK: U21.5 (I5); also elsewhere on the board
~CS1: U1.4 (I3); also elsewhere on the board
~CS2: U1.13 (I11); also elsewhere on the board
~CS_CTC1: U1.21 (O2); also elsewhere on the board
~CS_PIO1: U1.19 (O4); also elsewhere on the board
~CS_PIO2: U1.18 (O5); also elsewhere on the board
~CS_SIO1: U1.20 (O3); also elsewhere on the board
~IEO: U1.5 (I4); also elsewhere on the board
~PM1: U1.23 (O0); also elsewhere on the board
~WAIT: JP4.2 (B); also elsewhere on the board
~bIEI: U1.7 (I6); also elsewhere on the board
~bINT: D3.1 (K); also elsewhere on the board
~bIORQ_RAW: U21.2 (I2); also elsewhere on the board
~bIORQ: U1.8 (I7), U21.19 (IO1); also elsewhere on the board
~bM1: U1.6 (I5), U21.4 (I4); also elsewhere on the board
~bRD: U1.3 (I2); also elsewhere on the board
~bRESET: U1.2 (I1); also elsewhere on the board

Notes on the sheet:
ZILOG DATA DIR GAL22V10
INTERRUPT
INTERRUPT ACKNOWLEDGE DELAY GAL16V8
NOTE: ~{WAIT} RELIES ON 4700 OHM PULL UP RESISTOR ON PROCESSOR BOARD
INTERRUPT ACKNOWLEDGE CYCLE DELAY CIRCUIT

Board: 2 copper layers, 102 parts (0 on the bottom side), 210 nets, no tracks yet.
